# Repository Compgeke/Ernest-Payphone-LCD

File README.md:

# Ernest Payphone LCD
PCB to allow you to attach an LCD to an Ernest Telecom Payphone

This is useful for programming or even just general use. Confirmed to work on a D7, should work on the others too. Uses a standard 16x2 LCD, 14 pin ribbon cable and some pin header. Add resistor if your screen is backlit.

This screen is needed for local programming on the phones. See phone manuals for more information on how to program. 

Main project files are for KiCad if you want to remix or whatnot. If you just want to fab a PCB, download the gerbers zip file and send them to your favorite fab house.

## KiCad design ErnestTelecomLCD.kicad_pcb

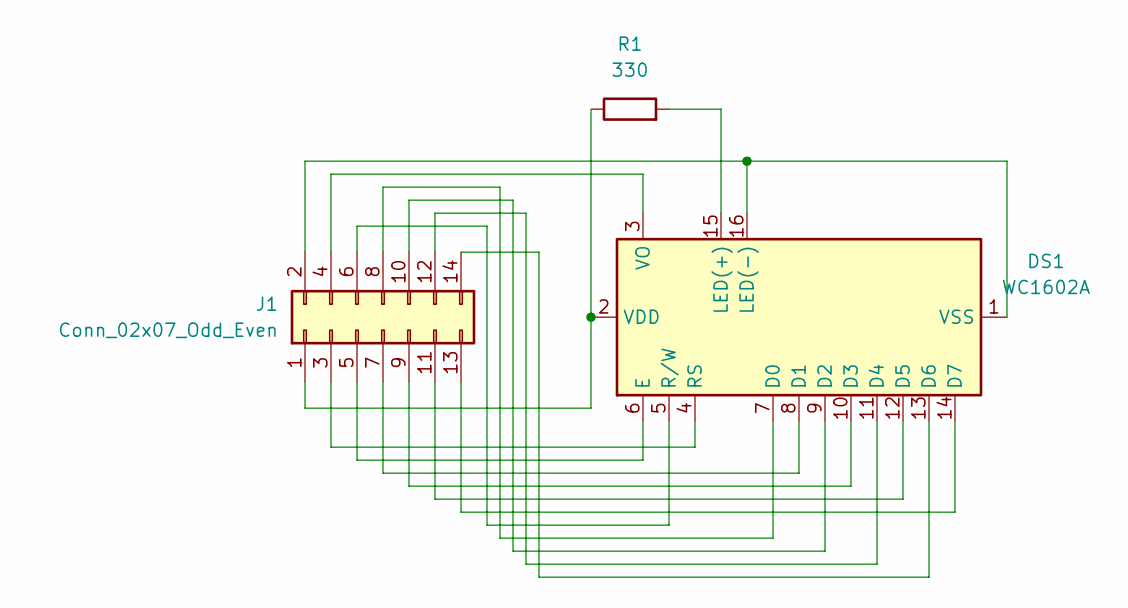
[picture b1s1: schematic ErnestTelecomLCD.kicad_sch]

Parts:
DS1: WC1602A
J1: Conn_02x07_Odd_Even; IDC-Header_2x07_P2.54mm_Horizontal
R1: 330; R_Box_L13.0mm_W4.0mm_P9.00mm

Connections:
unnamed: DS1.7 (D0), J1.8
unnamed: DS1.8 (D1), J1.7
unnamed: DS1.9 (D2), J1.10
unnamed: DS1.10 (D3), J1.9
unnamed: DS1.11 (D4), J1.12
unnamed: DS1.12 (D5), J1.11
unnamed: DS1.13 (D6), J1.14
unnamed: DS1.14 (D7), J1.13
unnamed: DS1.6 (E), J1.5
unnamed: DS1.15 (LED(+)), R1.2
unnamed: DS1.1 (VSS), DS1.16 (LED(-)), J1.2
unnamed: DS1.4 (RS), J1.3
unnamed: DS1.5 (R/W), J1.6
unnamed: DS1.2 (VDD), J1.1, R1.1
unnamed: DS1.3 (VO), J1.4

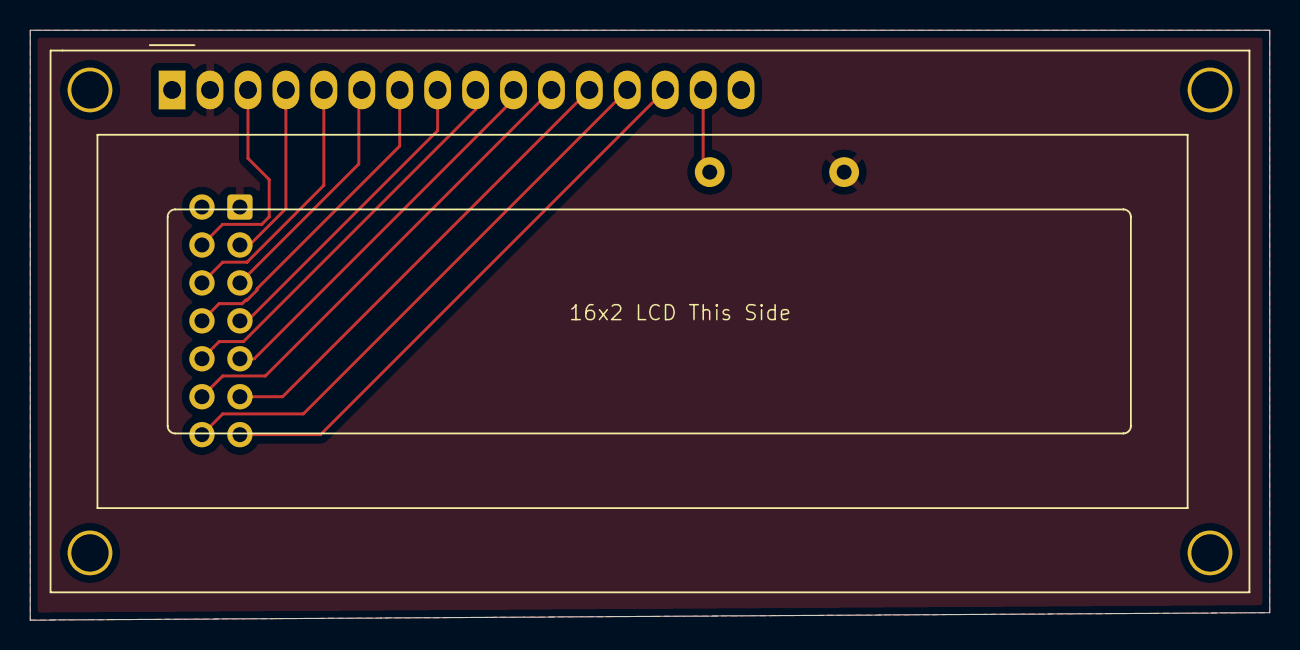
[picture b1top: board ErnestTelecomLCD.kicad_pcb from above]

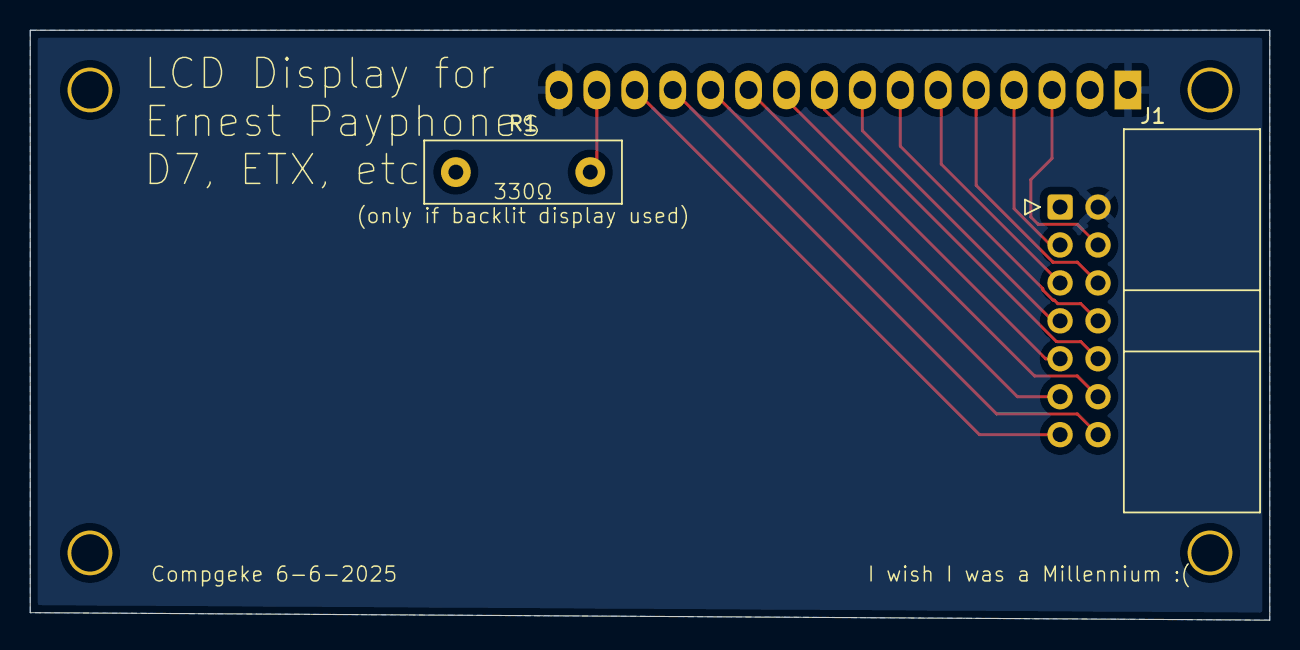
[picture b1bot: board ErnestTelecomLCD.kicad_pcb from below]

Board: 2 copper layers, 83.0 x 39.5 mm, 3 parts (2 on the bottom side), 15 nets.

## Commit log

2025-06-17 KiCad Files
2025-06-17 Added Gerber Files
